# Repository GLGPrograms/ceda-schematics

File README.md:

# Sanco 8003 schematics
This is the reverse engineered schematics of the Sanco 8003 French retrocomputer.

PCB is marked as Logic Systems Int'l FPX-290.

## Other resources
- [ROM Disassembly](https://github.com/GLGPrograms/ceda-rom-disassembly)

## Contributing
Please send help.

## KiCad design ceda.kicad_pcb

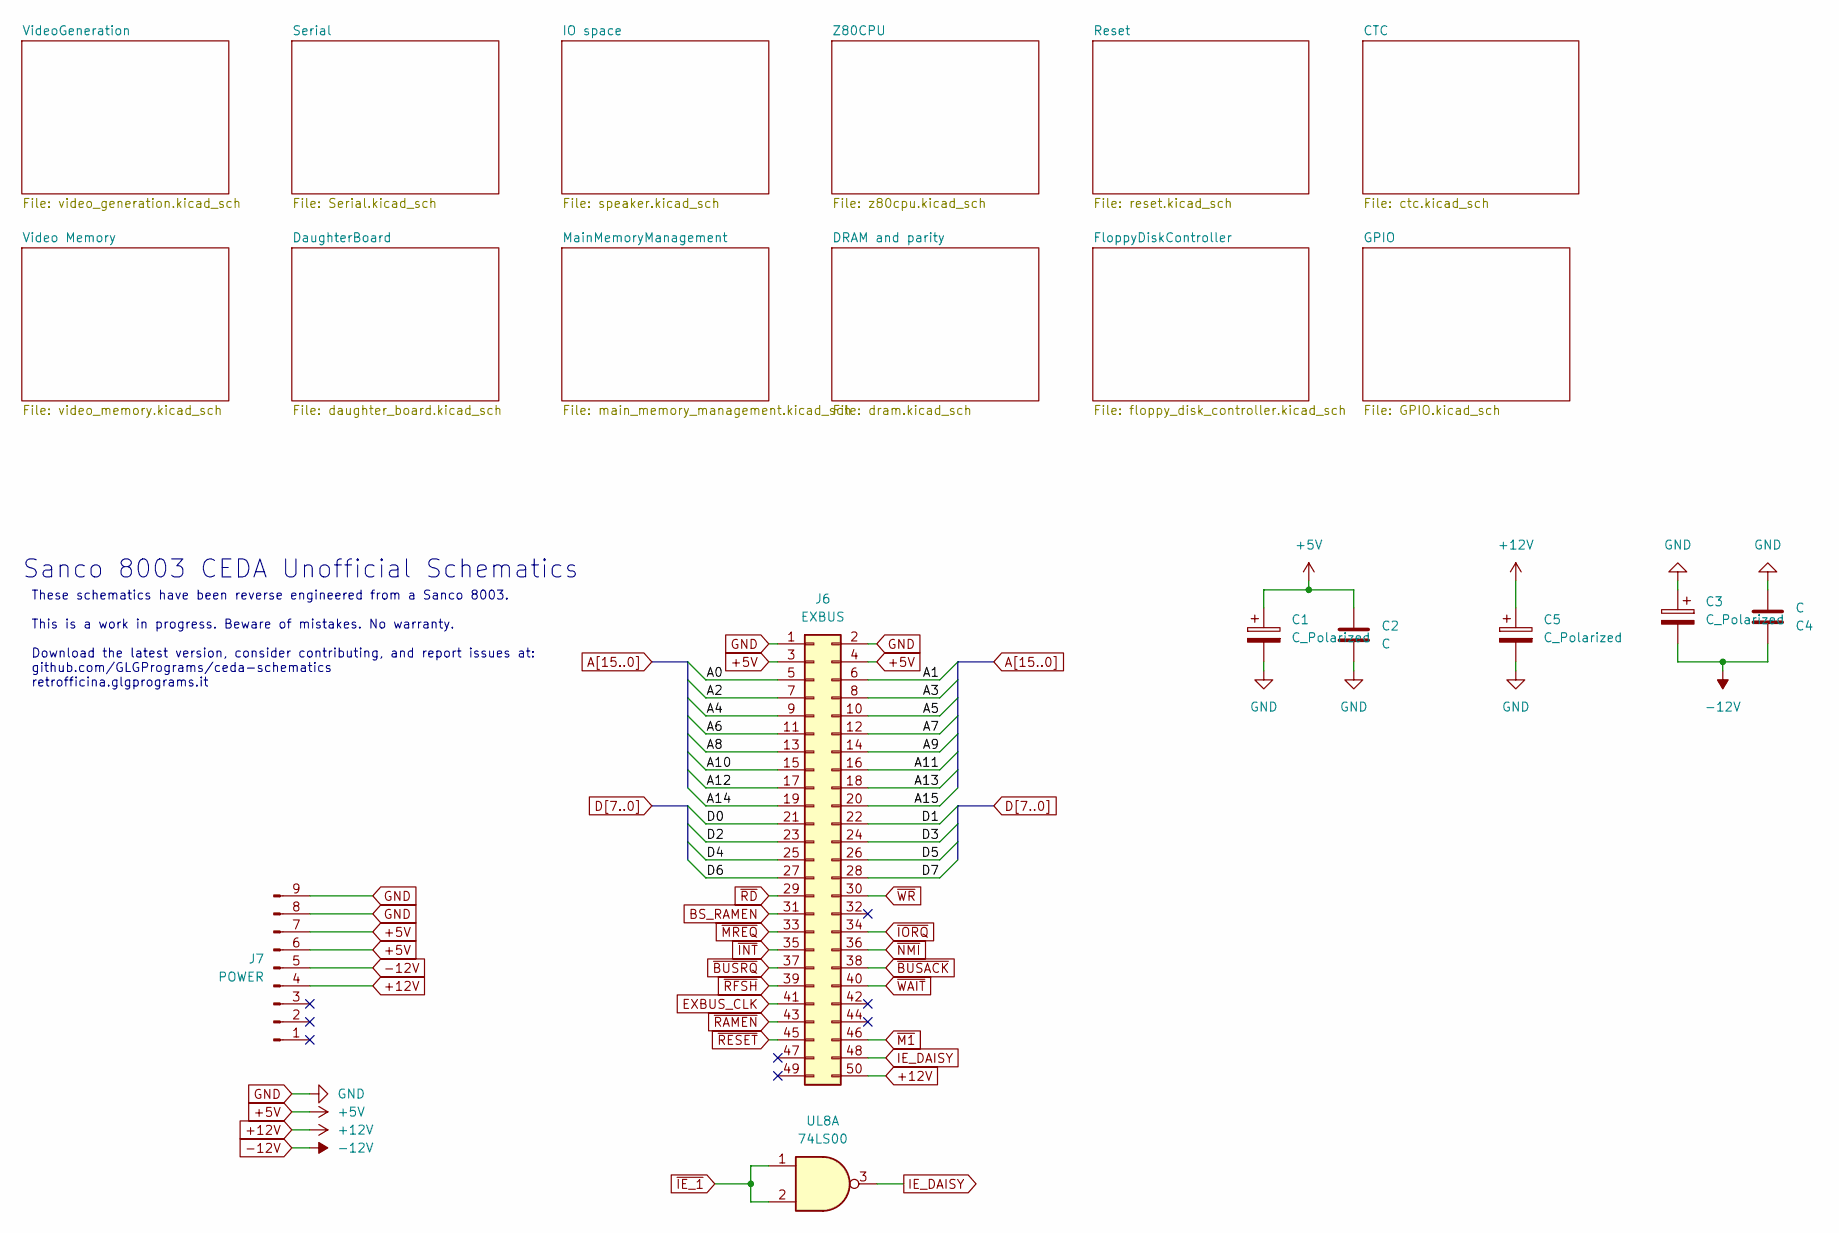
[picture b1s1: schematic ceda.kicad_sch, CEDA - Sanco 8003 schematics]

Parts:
C1, C3, C5: C_Polarized; CP_Radial_D5.0mm_P2.50mm
C2, C4: C; C_Disc_D4.3mm_W1.9mm_P5.00mm
J6: EXBUS; IDC-Header_2x25_P2.54mm_Vertical
J7: POWER; Molex_KK-396_5273-09A_1x09_P3.96mm_Vertical
UL8: 74LS00; DIP-14_W7.62mm

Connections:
+5V: C1.1, C2.1, J6.3, J6.4, J7.6, J7.7; also elsewhere on the board
+12V: C5.1, J6.50, J7.4; also elsewhere on the board
-12V: C3.2, C4.1, J7.5; also elsewhere on the board
A0: J6.5; also elsewhere on the board
A1: J6.6; also elsewhere on the board
A2: J6.7; also elsewhere on the board
A3: J6.8; also elsewhere on the board
A4: J6.9; also elsewhere on the board
A5: J6.10; also elsewhere on the board
A6: J6.11; also elsewhere on the board
A7: J6.12; also elsewhere on the board
A8: J6.13; also elsewhere on the board
A9: J6.14; also elsewhere on the board
A10: J6.15; also elsewhere on the board
A11: J6.16; also elsewhere on the board
A12: J6.17; also elsewhere on the board
A13: J6.18; also elsewhere on the board
A14: J6.19; also elsewhere on the board
A15: J6.20; also elsewhere on the board
BS_RAMEN: J6.31; also elsewhere on the board
D0: J6.21; also elsewhere on the board
D1: J6.22; also elsewhere on the board
D2: J6.23; also elsewhere on the board
D3: J6.24; also elsewhere on the board
D4: J6.25; also elsewhere on the board
D5: J6.26; also elsewhere on the board
D6: J6.27; also elsewhere on the board
D7: J6.28; also elsewhere on the board
EXBUS_CLK: J6.41; also elsewhere on the board
GND: C1.2, C2.2, C3.1, C4.2, C5.2, J6.1, J6.2, J7.8, J7.9; also elsewhere on the board
IE_DAISY: J6.48, UL8.3
~BUSACK: J6.38; also elsewhere on the board
~BUSRQ: J6.37; also elsewhere on the board
~IE_1: UL8.1, UL8.2; also elsewhere on the board
~INT: J6.35; also elsewhere on the board
~IORQ: J6.34; also elsewhere on the board
~M1: J6.46; also elsewhere on the board
~MREQ: J6.33; also elsewhere on the board
~NMI: J6.36; also elsewhere on the board
~RAMEN: J6.43; also elsewhere on the board
~RD: J6.29; also elsewhere on the board
~RESET: J6.45; also elsewhere on the board
~RFSH: J6.39; also elsewhere on the board
~WAIT: J6.40; also elsewhere on the board
~WR: J6.30; also elsewhere on the board

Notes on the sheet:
These schematics have been reverse engineered from a Sanco 8003. This is a work in progress. Beware of mistakes. No warranty. Download the latest version, consider contributing, and report issues at: github.com/GLGPrograms/ceda-schematics retrofficina.glgprograms.it
Sanco 8003 CEDA Unofficial Schematics

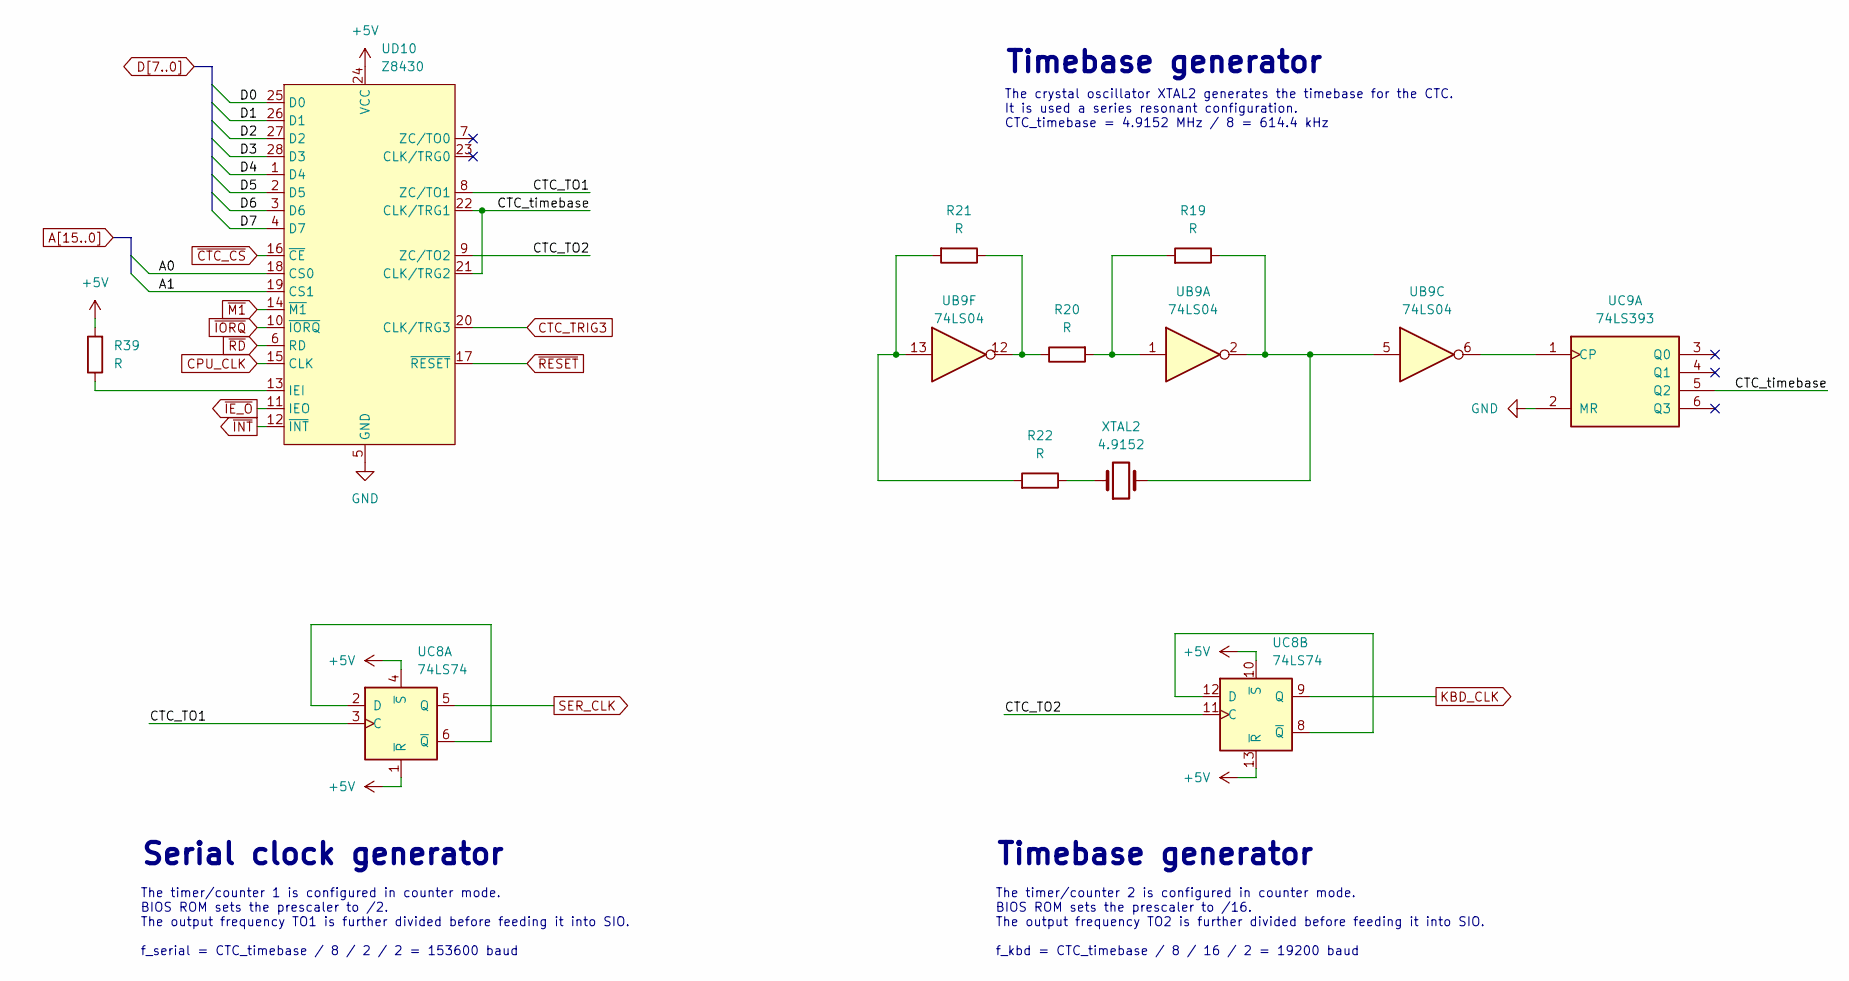
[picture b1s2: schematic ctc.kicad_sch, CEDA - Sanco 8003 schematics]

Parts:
R19, R20, R21, R22, R39: R; R_Axial_DIN0204_L3.6mm_D1.6mm_P5.08mm_Vertical
UB9: 74LS04; DIP-14_W7.62mm
UC8: 74LS74; DIP-14_W7.62mm
UC9: 74LS393; DIP-14_W7.62mm
UD10: Z8430; DIP-28_W15.24mm
XTAL2: 4.9152; Crystal_HC18-U_Vertical

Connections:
+5V: R39.2, UC8.1 (~R), UC8.4 (~S), UC8.10 (~S), UC8.13 (~R), UD10.24 (VCC); also elsewhere on the board
/CTC/CTC_TO1: UC8.3 (C), UD10.8 (ZC/TO1)
/CTC/CTC_TO2: UC8.11 (C), UD10.9 (ZC/TO2)
/CTC/CTC_timebase: UC9.5 (Q2), UD10.21 (CLK/TRG2), UD10.22 (CLK/TRG1)
A0: UD10.18 (CS0); also elsewhere on the board
A1: UD10.19 (CS1); also elsewhere on the board
CPU_CLK: UD10.15 (CLK); also elsewhere on the board
CTC_TRIG3: UD10.20 (CLK/TRG3); also elsewhere on the board
D0: UD10.25 (D0); also elsewhere on the board
D1: UD10.26 (D1); also elsewhere on the board
D2: UD10.27 (D2); also elsewhere on the board
D3: UD10.28 (D3); also elsewhere on the board
D4: UD10.1 (D4); also elsewhere on the board
D5: UD10.2 (D5); also elsewhere on the board
D6: UD10.3 (D6); also elsewhere on the board
D7: UD10.4 (D7); also elsewhere on the board
GND: UC9.2 (MR), UD10.5 (GND); also elsewhere on the board
KBD_CLK: UC8.9 (Q); also elsewhere on the board
unnamed: R19.1, UB9.2, UB9.5, XTAL2.2
unnamed: R19.2, R20.2, UB9.1
unnamed: R20.1, R21.1, UB9.12
unnamed: R21.2, R22.2, UB9.13
unnamed: R22.1, XTAL2.1
unnamed: UC8.2 (D), UC8.6 (~Q)
unnamed: UC8.8 (~Q), UC8.12 (D)
unnamed: UB9.6, UC9.1 (CP)
unnamed: R39.1, UD10.13 (IEI)
SER_CLK: UC8.5 (Q); also elsewhere on the board
~CTC_CS: UD10.16 (~CE); also elsewhere on the board
~IE_O: UD10.11 (IEO)
~INT: UD10.12 (~INT); also elsewhere on the board
~IORQ: UD10.10 (~IORQ); also elsewhere on the board
~M1: UD10.14 (~M1); also elsewhere on the board
~RD: UD10.6 (RD); also elsewhere on the board
~RESET: UD10.17 (~RESET); also elsewhere on the board

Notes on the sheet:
Serial clock generator
The timer/counter 2 is configured in counter mode. BIOS ROM sets the prescaler to /16. The output frequency TO2 is further divided before feeding it into SIO. f_kbd = CTC_timebase / 8 / 16 / 2 = 19200 baud
Timebase generator
The crystal oscillator XTAL2 generates the timebase for the CTC. It is used a series resonant configuration. CTC_timebase = 4.9152 MHz / 8 = 614.4 kHz
The timer/counter 1 is configured in counter mode. BIOS ROM sets the prescaler to /2. The output frequency TO1 is further divided before feeding it into SIO. f_serial = CTC_timebase / 8 / 2 / 2 = 153600 baud

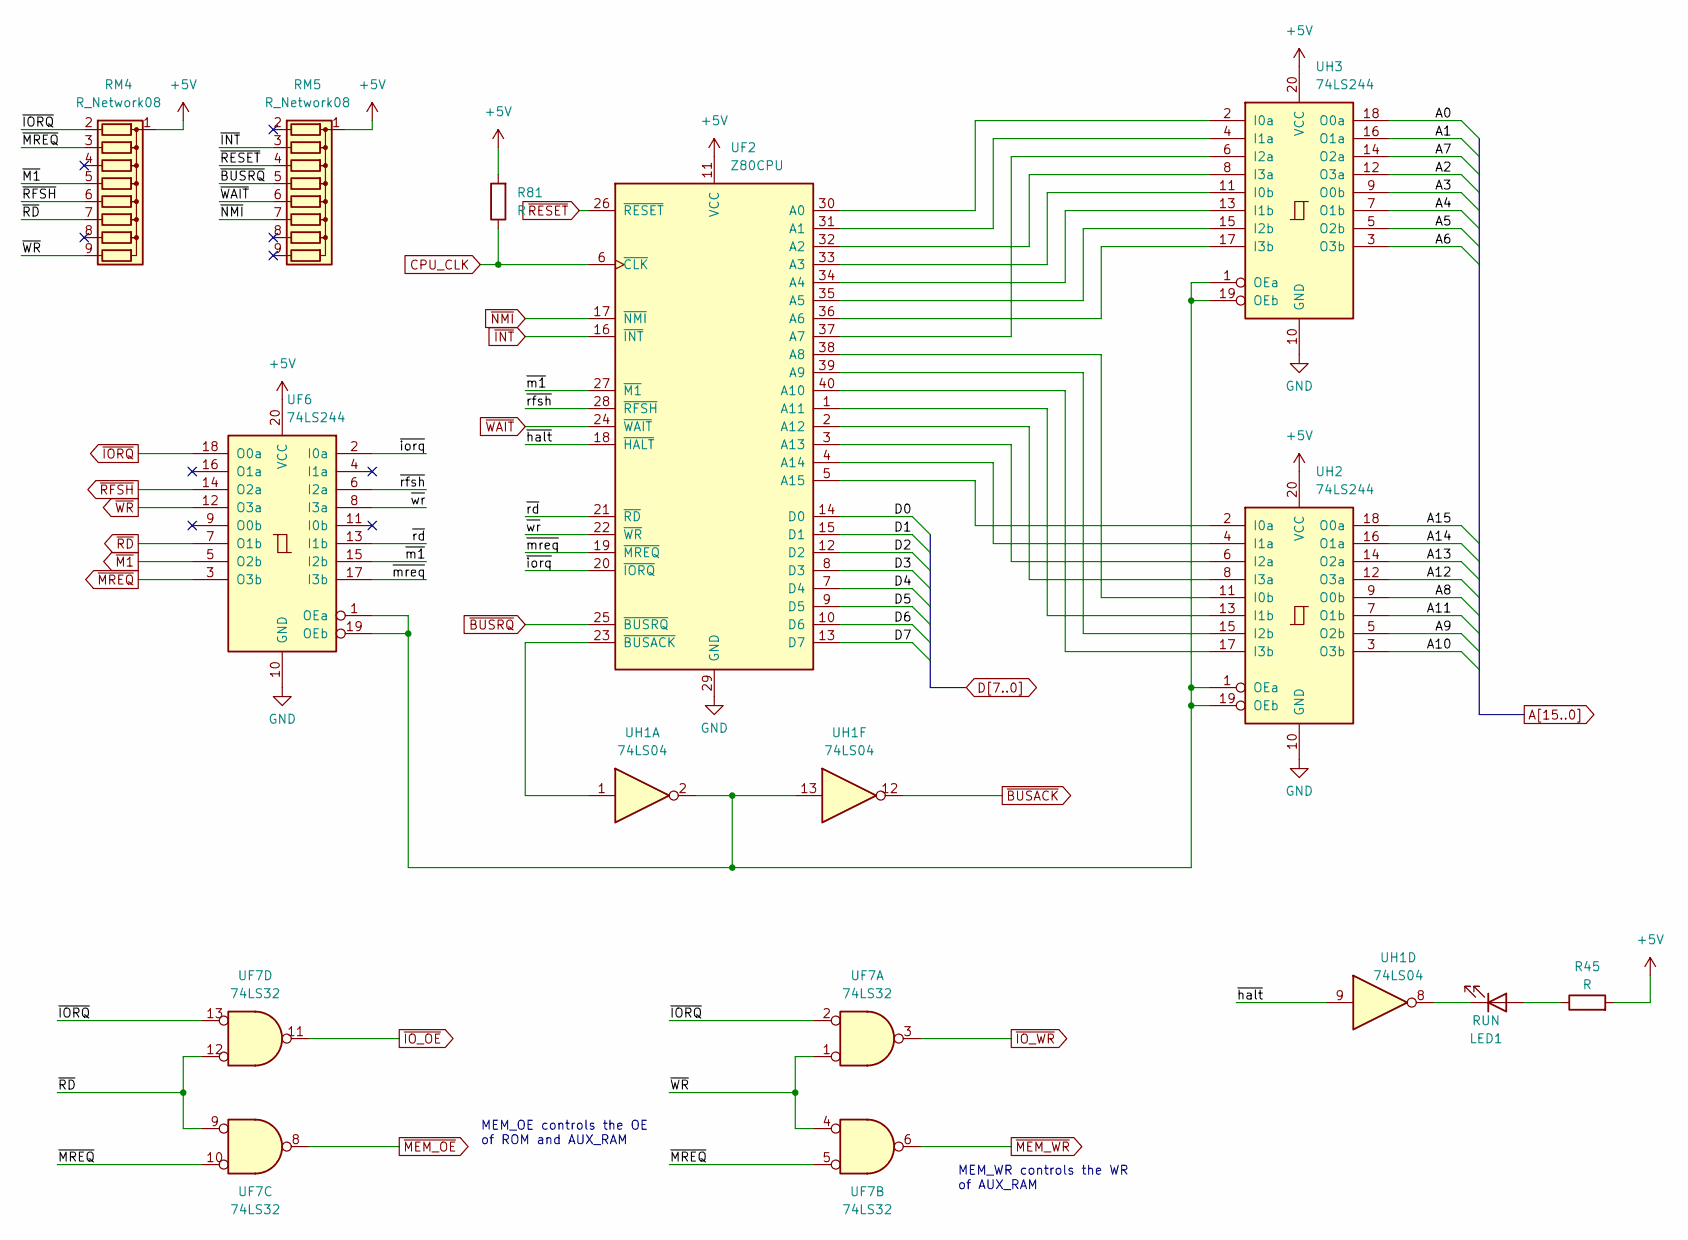
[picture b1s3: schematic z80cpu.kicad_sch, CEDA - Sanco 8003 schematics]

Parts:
LED1: RUN; LED_D3.0mm
R45, R81: R; R_Axial_DIN0204_L3.6mm_D1.6mm_P5.08mm_Vertical
RM4, RM5: R_Network08; R_Array_SIP9
UF2: Z80CPU; DIP-40_W15.24mm
UF6: 74LS244; DIP-20_W7.62mm
UF7: 74LS32; DIP-14_W7.62mm
UH1: 74LS04; DIP-14_W7.62mm
UH2, UH3: 74LS244; DIP-20_W7.62mm

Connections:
+5V: R45.2, R81.2, RM4.1 (common), RM5.1 (common), UF2.11 (VCC), UF6.20 (VCC), UH2.20 (VCC), UH3.20 (VCC); also elsewhere on the board
/Z80CPU/~halt: UF2.18 (~HALT), UH1.9
/Z80CPU/~iorq: UF2.20 (~IORQ), UF6.2 (I0a)
/Z80CPU/~m1: UF2.27 (~M1), UF6.15 (I2b)
/Z80CPU/~mreq: UF2.19 (~MREQ), UF6.17 (I3b)
/Z80CPU/~rd: UF2.21 (~RD), UF6.13 (I1b)
/Z80CPU/~rfsh: UF2.28 (~RFSH), UF6.6 (I2a)
/Z80CPU/~wr: UF2.22 (~WR), UF6.8 (I3a)
A0: UH3.18 (O0a); also elsewhere on the board
A1: UH3.16 (O1a); also elsewhere on the board
A2: UH3.12 (O3a); also elsewhere on the board
A3: UH3.9 (O0b); also elsewhere on the board
A4: UH3.7 (O1b); also elsewhere on the board
A5: UH3.5 (O2b); also elsewhere on the board
A6: UH3.3 (O3b); also elsewhere on the board
A7: UH3.14 (O2a); also elsewhere on the board
A8: UH2.9 (O0b); also elsewhere on the board
A9: UH2.5 (O2b); also elsewhere on the board
A10: UH2.3 (O3b); also elsewhere on the board
A11: UH2.7 (O1b); also elsewhere on the board
A12: UH2.12 (O3a); also elsewhere on the board
A13: UH2.14 (O2a); also elsewhere on the board
A14: UH2.16 (O1a); also elsewhere on the board
A15: UH2.18 (O0a); also elsewhere on the board
CPU_CLK: R81.1, UF2.6 (~CLK); also elsewhere on the board
D0: UF2.14 (D0); also elsewhere on the board
D1: UF2.15 (D1); also elsewhere on the board
D2: UF2.12 (D2); also elsewhere on the board
D3: UF2.8 (D3); also elsewhere on the board
D4: UF2.7 (D4); also elsewhere on the board
D5: UF2.9 (D5); also elsewhere on the board
D6: UF2.10 (D6); also elsewhere on the board
D7: UF2.13 (D7); also elsewhere on the board
GND: UF2.29 (GND), UF6.10 (GND), UH2.10 (GND), UH3.10 (GND); also elsewhere on the board
unnamed: LED1.2 (A), R45.1
unnamed: LED1.1 (K), UH1.8
unnamed: UF2.30 (A0), UH3.2 (I0a)
unnamed: UF2.31 (A1), UH3.4 (I1a)
unnamed: UF2.32 (A2), UH3.8 (I3a)
unnamed: UF2.33 (A3), UH3.11 (I0b)
unnamed: UF2.34 (A4), UH3.13 (I1b)
unnamed: UF2.35 (A5), UH3.15 (I2b)
unnamed: UF2.36 (A6), UH3.17 (I3b)
unnamed: UF2.37 (A7), UH3.6 (I2a)
unnamed: UF2.38 (A8), UH2.11 (I0b)
unnamed: UF2.39 (A9), UH2.15 (I2b)
unnamed: UF2.40 (A10), UH2.17 (I3b)
unnamed: UF2.1 (A11), UH2.13 (I1b)
unnamed: UF2.2 (A12), UH2.8 (I3a)
unnamed: UF2.3 (A13), UH2.6 (I2a)
unnamed: UF2.4 (A14), UH2.4 (I1a)
unnamed: UF2.5 (A15), UH2.2 (I0a)
unnamed: UF2.23 (~BUSACK), UH1.1
unnamed: UF6.1 (OEa), UF6.19 (OEb), UH1.2, UH1.13, UH2.1 (OEa), UH2.19 (OEb), UH3.1 (OEa), UH3.19 (OEb)
~BUSACK: UH1.12; also elsewhere on the board
~BUSRQ: RM5.5 (R4), UF2.25 (~BUSRQ); also elsewhere on the board
~INT: RM5.3 (R2), UF2.16 (~INT); also elsewhere on the board
~IORQ: RM4.2 (R1), UF6.18 (O0a), UF7.2, UF7.13; also elsewhere on the board
~IO_OE: UF7.11; also elsewhere on the board
~IO_WR: UF7.3; also elsewhere on the board
~M1: RM4.5 (R4), UF6.5 (O2b); also elsewhere on the board
~MEM_OE: UF7.8; also elsewhere on the board
~MEM_WR: UF7.6; also elsewhere on the board
~MREQ: RM4.3 (R2), UF6.3 (O3b), UF7.5, UF7.10; also elsewhere on the board
~NMI: RM5.7 (R6), UF2.17 (~NMI); also elsewhere on the board
~RD: RM4.7 (R6), UF6.7 (O1b), UF7.9, UF7.12; also elsewhere on the board
~RESET: RM5.4 (R3), UF2.26 (~RESET); also elsewhere on the board
~RFSH: RM4.6 (R5), UF6.14 (O2a); also elsewhere on the board
~WAIT: RM5.6 (R5), UF2.24 (~WAIT); also elsewhere on the board
~WR: RM4.9 (R8), UF6.12 (O3a), UF7.1, UF7.4; also elsewhere on the board

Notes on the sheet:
MEM_OE controls the OE of ROM and AUX_RAM
MEM_WR controls the WR of AUX_RAM

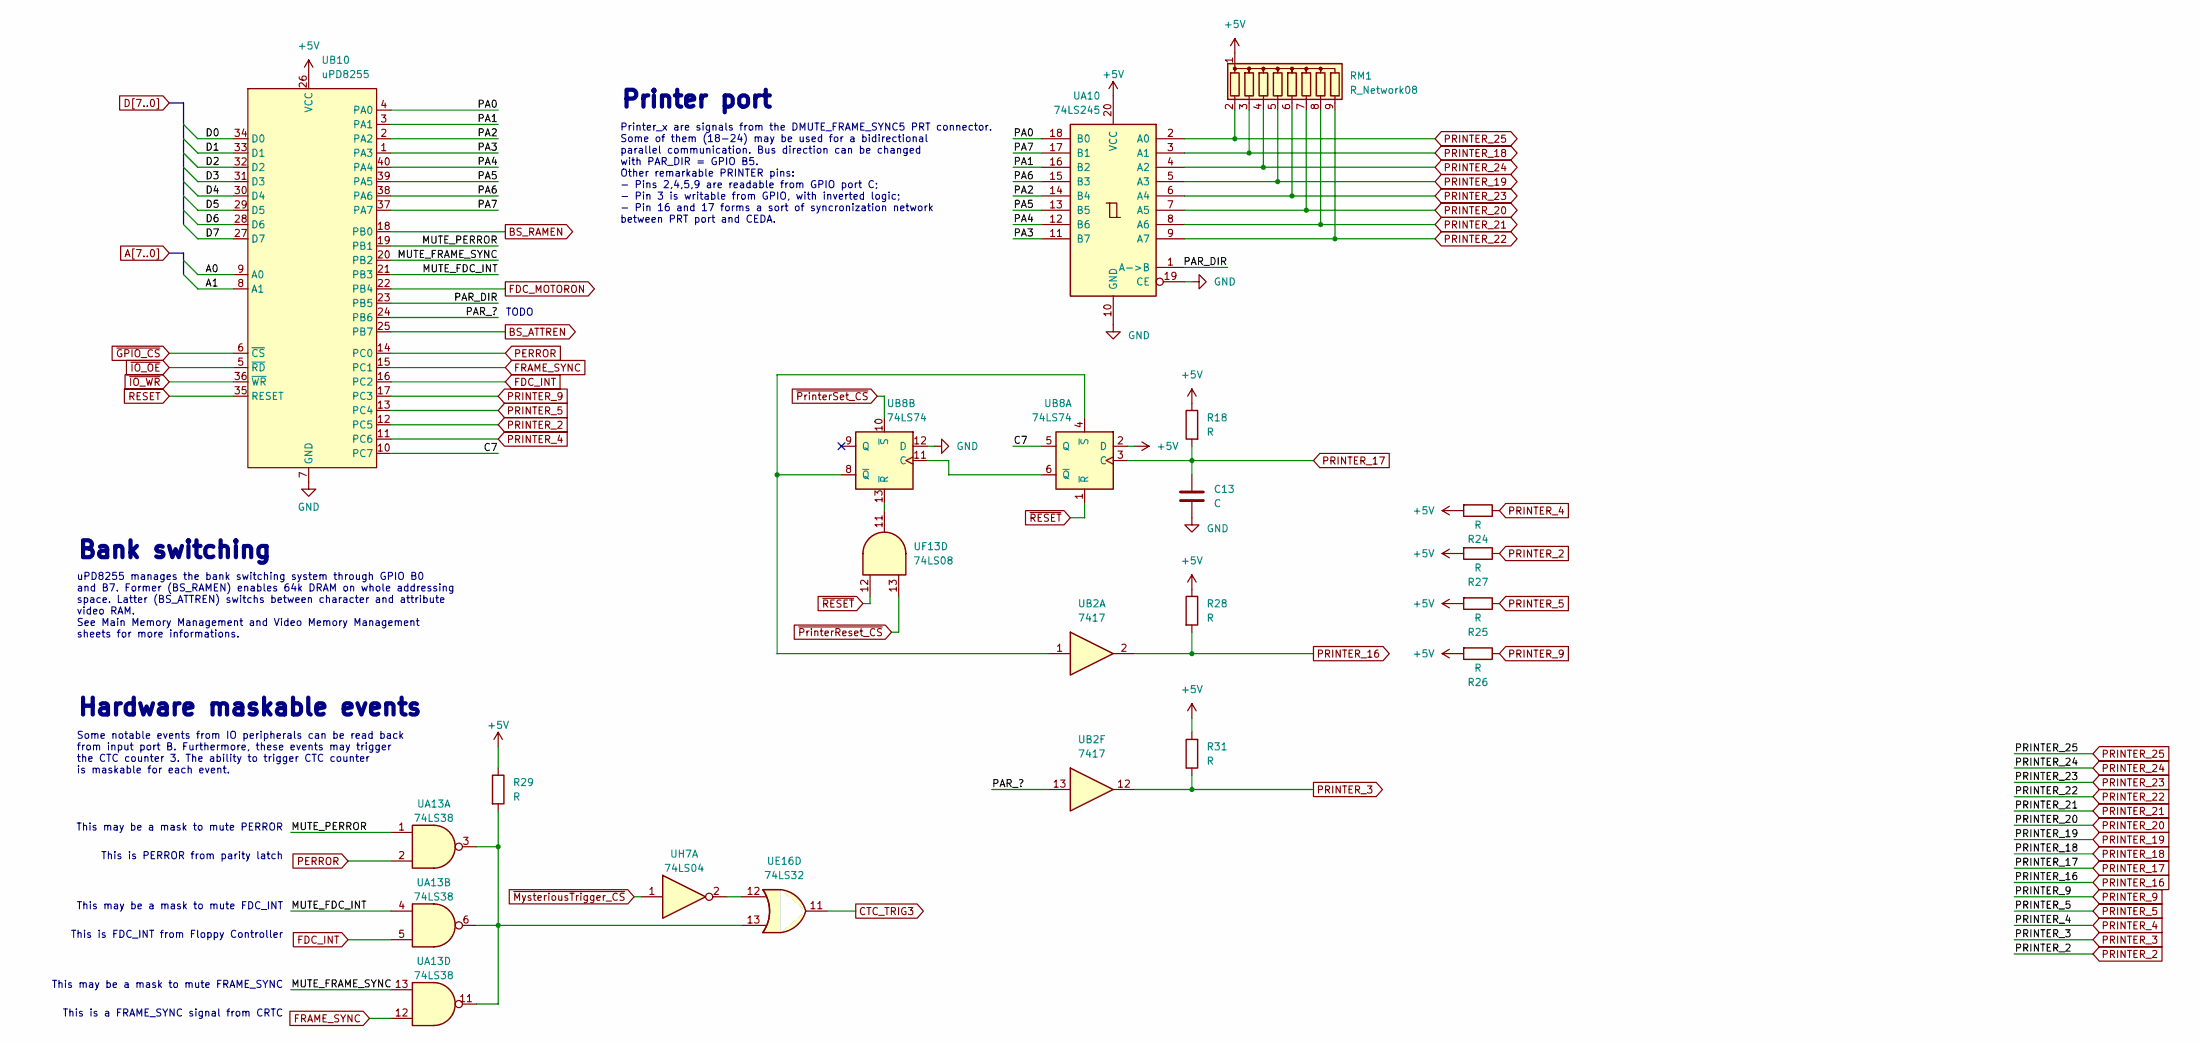
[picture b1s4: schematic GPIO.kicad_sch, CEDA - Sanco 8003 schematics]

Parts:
C13: C; C_Disc_D4.3mm_W1.9mm_P5.00mm
R18, R24, R25, R26, R27, R28, R29, R31: R; R_Axial_DIN0204_L3.6mm_D1.6mm_P5.08mm_Vertical
RM1: R_Network08; R_Array_SIP9
UA10: 74LS245; DIP-20_W7.62mm
UA13: 74LS38; DIP-14_W7.62mm
UB2: 7417; DIP-14_W7.62mm
UB8: 74LS74; DIP-14_W7.62mm
UB10: uPD8255; DIP-40_W15.24mm
UE16: 74LS32; DIP-14_W7.62mm
UF13: 74LS08; DIP-14_W7.62mm
UH7: 74LS04; DIP-14_W7.62mm

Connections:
+5V: R18.1, R24.2, R25.2, R26.2, R27.2, R28.1, R29.1, R31.2, RM1.1 (common), UA10.20 (VCC), UB8.2 (D), UB10.26 (VCC); also elsewhere on the board
/GPIO/C7: UB8.5 (Q), UB10.10 (PC7)
/GPIO/MUTE_FDC_INT: UA13.4, UB10.21 (PB3)
/GPIO/MUTE_FRAME_SYNC: UA13.13, UB10.20 (PB2)
/GPIO/MUTE_PERROR: UA13.1, UB10.19 (PB1)
/GPIO/PA0: UA10.18 (B0), UB10.4 (PA0)
/GPIO/PA1: UA10.16 (B2), UB10.3 (PA1)
/GPIO/PA2: UA10.14 (B4), UB10.2 (PA2)
/GPIO/PA3: UA10.11 (B7), UB10.1 (PA3)
/GPIO/PA4: UA10.12 (B6), UB10.40 (PA4)
/GPIO/PA5: UA10.13 (B5), UB10.39 (PA5)
/GPIO/PA6: UA10.15 (B3), UB10.38 (PA6)
/GPIO/PA7: UA10.17 (B1), UB10.37 (PA7)
/GPIO/PAR_?: UB2.13, UB10.24 (PB6)
/GPIO/PAR_DIR: UA10.1 (A->B), UB10.23 (PB5)
A0: UB10.9 (A0); also elsewhere on the board
A1: UB10.8 (A1); also elsewhere on the board
BS_ATTREN: UB10.25 (PB7); also elsewhere on the board
BS_RAMEN: UB10.18 (PB0); also elsewhere on the board
CTC_TRIG3: UE16.11; also elsewhere on the board
D0: UB10.34 (D0); also elsewhere on the board
D1: UB10.33 (D1); also elsewhere on the board
D2: UB10.32 (D2); also elsewhere on the board
D3: UB10.31 (D3); also elsewhere on the board
D4: UB10.30 (D4); also elsewhere on the board
D5: UB10.29 (D5); also elsewhere on the board
D6: UB10.28 (D6); also elsewhere on the board
D7: UB10.27 (D7); also elsewhere on the board
FDC_INT: UA13.5, UB10.16 (PC2); also elsewhere on the board
FDC_MOTORON: UB10.22 (PB4); also elsewhere on the board
FRAME_SYNC: UA13.12, UB10.15 (PC1); also elsewhere on the board
GND: C13.2, UA10.10 (GND), UA10.19 (CE), UB8.12 (D), UB10.7 (GND); also elsewhere on the board
unnamed: R29.2, UA13.3, UA13.6, UA13.11, UE16.13
unnamed: UB8.6 (~Q), UB8.11 (C)
unnamed: UB2.1, UB8.4 (~S), UB8.8 (~Q)
unnamed: UB8.13 (~R), UF13.11
unnamed: UE16.12, UH7.2
PERROR: UA13.2, UB10.14 (PC0); also elsewhere on the board
PRINTER_2: R27.1, UB10.12 (PC5); also elsewhere on the board
PRINTER_3: R31.1, UB2.12; also elsewhere on the board
PRINTER_4: R24.1, UB10.11 (PC6); also elsewhere on the board
PRINTER_5: R25.1, UB10.13 (PC4); also elsewhere on the board
PRINTER_9: R26.1, UB10.17 (PC3); also elsewhere on the board
PRINTER_16: R28.2, UB2.2; also elsewhere on the board
PRINTER_17: C13.1, R18.2, UB8.3 (C); also elsewhere on the board
PRINTER_18: RM1.3 (R2), UA10.3 (A1); also elsewhere on the board
PRINTER_19: RM1.5 (R4), UA10.5 (A3); also elsewhere on the board
PRINTER_20: RM1.7 (R6), UA10.7 (A5); also elsewhere on the board
PRINTER_21: RM1.8 (R7), UA10.8 (A6); also elsewhere on the board
PRINTER_22: RM1.9 (R8), UA10.9 (A7); also elsewhere on the board
PRINTER_23: RM1.6 (R5), UA10.6 (A4); also elsewhere on the board
PRINTER_24: RM1.4 (R3), UA10.4 (A2); also elsewhere on the board
PRINTER_25: RM1.2 (R1), UA10.2 (A0); also elsewhere on the board
RESET: UB10.35 (RESET); also elsewhere on the board
~GPIO_CS: UB10.6 (~CS); also elsewhere on the board
~IO_OE: UB10.5 (~RD); also elsewhere on the board
~IO_WR: UB10.36 (~WR); also elsewhere on the board
~MysteriousTrigger_CS: UH7.1; also elsewhere on the board
~PrinterReset_CS: UF13.13; also elsewhere on the board
~PrinterSet_CS: UB8.10 (~S); also elsewhere on the board
~RESET: UB8.1 (~R), UF13.12; also elsewhere on the board

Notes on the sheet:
Printer_x are signals from the DMUTE_FRAME_SYNC5 PRT connector. Some of them (18-24) may be used for a bidirectional parallel communication. Bus direction can be changed with PAR_DIR = GPIO B5. Other remarkable PRINTER pins: - Pins 2,4,5,9 are readable from GPIO port C; - Pin 3 is writable from GPI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
This is PERROR from parity latch
This may be a mask to mute FRAME_SYNC
TODO
This is FDC_INT from Floppy Controller
Some notable events from IO peripherals can be read back from input port B. Furthermore, these events may trigger the CTC counter 3. The ability to trigger CTC counter is maskable for each event.
This is a FRAME_SYNC signal from CRTC
This may be a mask to mute FDC_INT
Hardware maskable events
Bank switching
uPD8255 manages the bank switching system through GPIO B0 and B7. Former (BS_RAMEN) enables 64k DRAM on whole addressing space. Latter (BS_ATTREN) switchs between character and attribute video RAM. See Main Memory Management and Video Memory Management sheets for more informations.
This may be a mask to mute PERROR
Printer port
